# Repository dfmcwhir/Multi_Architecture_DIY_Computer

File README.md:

# Multi_Architecture_DIY_Computer
A DIY computer system that uses a common backplane with swappable 8-bit CPU and add-on cards<BR><br>

Up front, I will state the following:
  1. I started the project for my own learning and enjoyment. There will be documentation shortfalls and hardware and SW bugs that I missed and/or fixed and forgot about. There will also be plenty of poor design choices and probletunities for improvement. 
  2. Most of the electrical designs borrow ideas/circuits from other peoples work and I have modified them to work in my systems. I will try to make sure I document where I got what from.
  3. For the software and firmware, initially I was doing my own development, but I'm not a coder so I progress was really slow/non-existent. More recently, I have started using AI which has led to a lot of progress. Really all the software and firmware in this project is either a slight modifications of other people's code or done by AI.

<br>
<h2> The Concept </h2>
The initial idea as I wrote it in my notes app was:<br>
<quote>
  <b><i></i>Idea for a retro computer "system" that uses various cards in the ISA format with a passive ISA back plane. Ideally the most of the individual ISA cards will be less that 100mmx100mm for cheaper PCB prices which limits them to 8-bit isa cards.

Ideally cpu and interface cards should be inter changeable, so that interface cards can be used with multiple different types of CPU boards. That may require jumpers/switches to change logic level of some control signals and/or to set address decoding.

Possible CPU cards:
  - 6502 - Based on Ben Eater's design
  - 8085 - Similar to the MiniMax 8085?
  - 8088 - IBM XT compatible-ish
  - 6809 - based on Grant Searle's design 
  - Z80 - TRS-80 compatible?
  - ESP32 - For giggles - Would need some sort of multiplexing/latching to generate the data, address, and control busses from the GPIO pins
  - ATMEGA328? - For giggles - Would need some sort of multiplexing/latching to generate the data, address, and control busses from the GPIO pins 

Possible interface cards:
  - Retro video card - MC6847 based. Similar to Kiran Tomlinson's blog post
  - Atmel based keyboard/display/serial - Based on Grant Searle's design
  - Memory expansion
  - Storage controller - ideally the overall system would be compatible with the PicoMem I/O card but a dedicated storage controller maybe required/desired.
</b></i>
</quote>
<br>
So far I have done the 6502 and 8085 CPU cards with the Z80 on the way. The plans for the add-cards changed over time, I didn't do all the ones listed (yet), but I have a number of others. Most of them have ISA_6502 in the name, because that is the CPU I started with, but should at least theoretically be compatible with other CPU cards if they are designed to interface with the bus as I have defined it and with the correct software.

<h2> The "ISA" Bus </h2>
<p>To make it very clear, I am using the physical ISA bus for interfacing but in no way indicating that it meets any ISA specification or standards. Putting a normal ISA card into the system will almost definitely not work and may damage everything. </p>
<p>With that out of the way, when I started designing the system, I tried to match the functions of the signals of my card to the signals functions/names of the standard ISA bus. The idea being, that it would make it easier to insure CPU card compatibility with the add-on cards that way. The matching to the standard ISA pin functions has drifted over time.</p>

<H2>Current bus description</H2>
<table><thead><tr><th>Pin</th><th>Name</th><th>Dir</th><th>Description</th></tr></thead><tbody>
<tr><td>A1</td><td>/I/O CH CK</td><td>IN</td><td>/IOen. Active low; indicates an I/O operation</td></tr>
<tr><td>A2</td><td>D7</td><td>IN/OUT</td><td>Data bit 7</td></tr>
<tr><td>A3</td><td>D6</td><td>IN/OUT</td><td>Data bit 6</td></tr>
<tr><td>A4</td><td>D5</td><td>IN/OUT</td><td>Data bit 5</td></tr>
<tr><td>A5</td><td>D4</td><td>IN/OUT</td><td>Data bit 4</td></tr>
<tr><td>A6</td><td>D3</td><td>IN/OUT</td><td>Data bit 3</td></tr>
<tr><td>A7</td><td>D2</td><td>IN/OUT</td><td>Data bit 2</td></tr>
<tr><td>A8</td><td>D1</td><td>IN/OUT</td><td>Data bit 1</td></tr>
<tr><td>A9</td><td>D0</td><td>IN/OUT&gt;</td><td>Data bit 0</td></tr>
<tr><td>A10</td><td>I/O CH RDY</td><td>IN</td><td>IOrdy or /WAIT, pulled low to lengthen memory cycles or pause the CPU (depending on the CPU card)*</td></tr>
<tr><td>A11</td><td>AEN</td><td>OUT</td><td>Address enable; Not currently used</td></tr>
<tr><td>A12</td><td>A19</td><td>OUT</td><td>Address bit 19 or BA19; Used for memory bank selection</td></tr>
<tr><td>A13</td><td>A18</td><td>OUT</td><td>Address bit 18 or BA18; Used for memory bank selection</td></tr>
<tr><td>A14</td><td>A17</td><td>OUT</td><td>Address bit 17 or BA17; Used for memory bank selection</td></tr>
<tr><td>A15</td><td>A16</td><td>OUT</td><td>Address bit 16 or BA19; Used for memory bank selection</td></tr>
<tr><td>A16</td><td>A15</td><td>OUT</td><td>Address bit 15</td></tr>
<tr><td>A17</td><td>A14</td><td>OUT</td><td>Address bit 14</td></tr>
<tr><td>A18</td><td>A13</td><td>OUT</td><td>Address bit 13</td></tr>
<tr><td>A19</td><td>A12</td><td>OUT</td><td>Address bit 12</td></tr>
<tr><td>A20</td><td>A11</td><td>OUT</td><td>Address bit 11</td></tr>
<tr><td>A21</td><td>A10</td><td>OUT</td><td>Address bit 10</td></tr>
<tr><td>A22</td><td>A9</td><td>OUT</td><td>Address bit 9</td></tr>
<tr><td>A23</td><td>A8</td><td>OUT</td><td>Address bit 8</td></tr>
<tr><td>A24</td><td>A7</td><td>OUT</td><td>Address bit 7</td></tr>
<tr><td>A25</td><td>A6</td><td>OUT</td><td>Address bit 6</td></tr>
<tr><td>A26</td><td>A5</td><td>OUT</td><td>Address bit 5</td></tr>
<tr><td>A27</td><td>A4</td><td>OUT</td><td>Address bit 4</td></tr>
<tr><td>A28</td><td>A3</td><td>OUT</td><td>Address bit 3</td></tr>
<tr><td>A29</td><td>A2</td><td>OUT</td><td>Address bit 2</td></tr>
<tr><td>A30</td><td>A1</td><td>OUT</td><td>Address bit 1</td></tr>
<tr><td>A31</td><td>A0</td><td>OUT</td><td>Address bit 0</td></tr>
<tr><td>B1</td><td><abbr title="Ground">GND</abbr></td><td>Ground</td><td></td>
</tr><tr><td>B2</td><td>RESET</td><td>OUT</td><td>Active low to reset or initialize system logic</td></tr>
<tr><td>B3</td><td>+5V</td><td>+5 <abbr title="Volts Direct Current">VDC</abbr></td><td></td></tr>
<tr><td>B4</td><td>IRQ2</td><td>IN</td><td>Interrupt Request 2; I/O card </td></tr>
<tr><td>B5</td><td>-5VDC</td><td>-5 VDC</td><td>Not Currently used</td></tr>
<tr><td>B6</td><td>DRQ2</td><td>IN</td><td>/DMA; Not used/tested by any add-on cards yet, but should put CPU in state for DMA operations*</td></tr>
<tr><td>B7</td><td>-12VDC</td><td>-12 VDC</td><td>Not Currently used</td></tr>
<tr><td>B8</td><td>/NOWS</td><td>IN</td><td>/STRETCH (CLK stretch); When Low should slow down the clock*</td></tr>
<tr><td>B9</td><td>+12VDC</td><td>+12 VDC</td><td>Not Currently used</td></tr>
<tr><td>B10</td><td>GND</td><td>Ground</td><td></td></tr>
<tr><td>B11</td><td>/SMEMW</td><td>OUT</td><td>Originally intended as /MEMw, but may now be a general Write*</td></tr>
<tr><td>B12</td><td>/SMEMR</td><td>OUT</td><td>Originally intended as /MEMr, but may now be a general Read*</td></tr>
<tr><td>B13</td><td>/IOW</td><td>OUT</td><td>/IOw (/IOen + /Write)*</td></tr>
<tr><td>B14</td><td>/IOR</td><td>OUT</td><td>/IOr (/IOen + /Read + Clk)*</td></tr>
<tr><td>B15</td><td>/DACK3</td><td>OUT</td><td>Not currently used</td></tr>
<tr><td>B16</td><td>DRQ3</td><td>IN</td><td>Not currently used</td></tr>
<tr><td>B17</td><td>/DACK1</td><td>OUT</td><td>Not currently used</td></tr>
<tr><td>B18</td><td>DRQ1</td><td>IN</td><td>Not currently used</td></tr>
<tr><td>B19</td><td>/REFRESH</td><td>IN/OUT</td><td>Not currently used</td></tr>
<tr><td>B20</td><td>CLOCK</td><td>OUT</td><td>/CLK (inverted clock)</td></tr>
<tr><td>B21</td><td>IRQ7</td><td>IN</td><td>Interrupt Request 7, Possibly sound card or SPI interface</td></tr>
<tr><td>B22</td><td>IRQ6</td><td>IN</td><td>Interrupt Request 6; Possibly display/kb</td></tr>
<tr><td>B23</td><td>IRQ5</td><td>IN</td><td>Interrupt Request 5; Usually KB/Display</td></tr>
<tr><td>B24</td><td>IRQ4</td><td>IN</td><td>Interrupt Request 4; I/O card I2C interface</td></tr>
<tr><td>B25</td><td>IRQ3</td><td>IN</td><td>Interrupt Request 3; Serial Card</td></tr>
<tr><td>B26</td><td>/DACK2</td><td>OUT</td><td>Not currently used</td></tr>
<tr><td>B27</td><td>T/C</td><td>OUT</td><td>Raw oscilator clock (2 x CLK) on some CPU cards(</td></tr>
<tr><td>B28</td><td>ALE</td><td>OUT</td><td>Not currently used</td></tr>
<tr><td>B29</td><td>+5V</td><td>+5 VDC</td><td></td></tr>
<tr><td>B30</td><td>OSC</td><td>OUT</td><td>CLK used by CPU and most circuits. In some CPU cards it is 1/2 of the osc frequency</td></tr>
<tr><td>B31</td><td>GND</td><td>Ground</td><td></td></tr>
<tr><td></td><td></td><td></td><td></td></tr>
</tbody></table>
<h3>Notes about some signals:</h3>
<p> /MEMw and /MEMr were initially derived from the R/nW signal on the 6502 card and either /ROMen or /RAMen. As things got more complex, it became necessary to have read and write signals that were available during I/O operations (/IOen) but were not connected to the clock. So now /MEMw and /MEMr on the bus could (depending on the CPU card) be active anytime either an I/O or Memory operation is happening. This means that add-on cards, if a memory read or write is needed, the /MEMw and MEMr signals should be qualified as being in memory by the address or at least by /IOen not being active.</p>
<p>The way /IOr is used on some add-on cards requires it to be active only when the CLK is high, so that is the way it is decoded on the bus. If a read from I/O that isn't dependent on the CLK being high is required (also required on some cards) then a local /read should be decoded from the /IOen and MEMr or /IOen and /IOw not active. /IOw is independent from the clk</p>
<p>Initially the /DMA (/DRQ2) signal was provided for simple DMA operations that Ben Eater describes for his VGA card implementaion. I have never used it and it maybe incompatible with some CPU cards.</p>
<p>IOrdy (or /WAIT) and /STRETCH were implemented on the 6502 CPU Rev2 card and haven't been tested yet. The difference is that /WAIT stops the CPU but CLK and /CLK continue to run. /Stretch stops CLK and /CLK. An Add-card would assert /Stretch then use the TC (2XOSC) raw oscillator signal to count some number of cycles before de-asserting it. On some CPU cards neither signal is implemented at all (like the 8085 CPU Rev1) and on others (like the Z80 CPU rev1) /STRETCH and /WAIT are the same (both are /STRETCH). I don't think any cards require these signals/features if operated at <4MHz. </p>

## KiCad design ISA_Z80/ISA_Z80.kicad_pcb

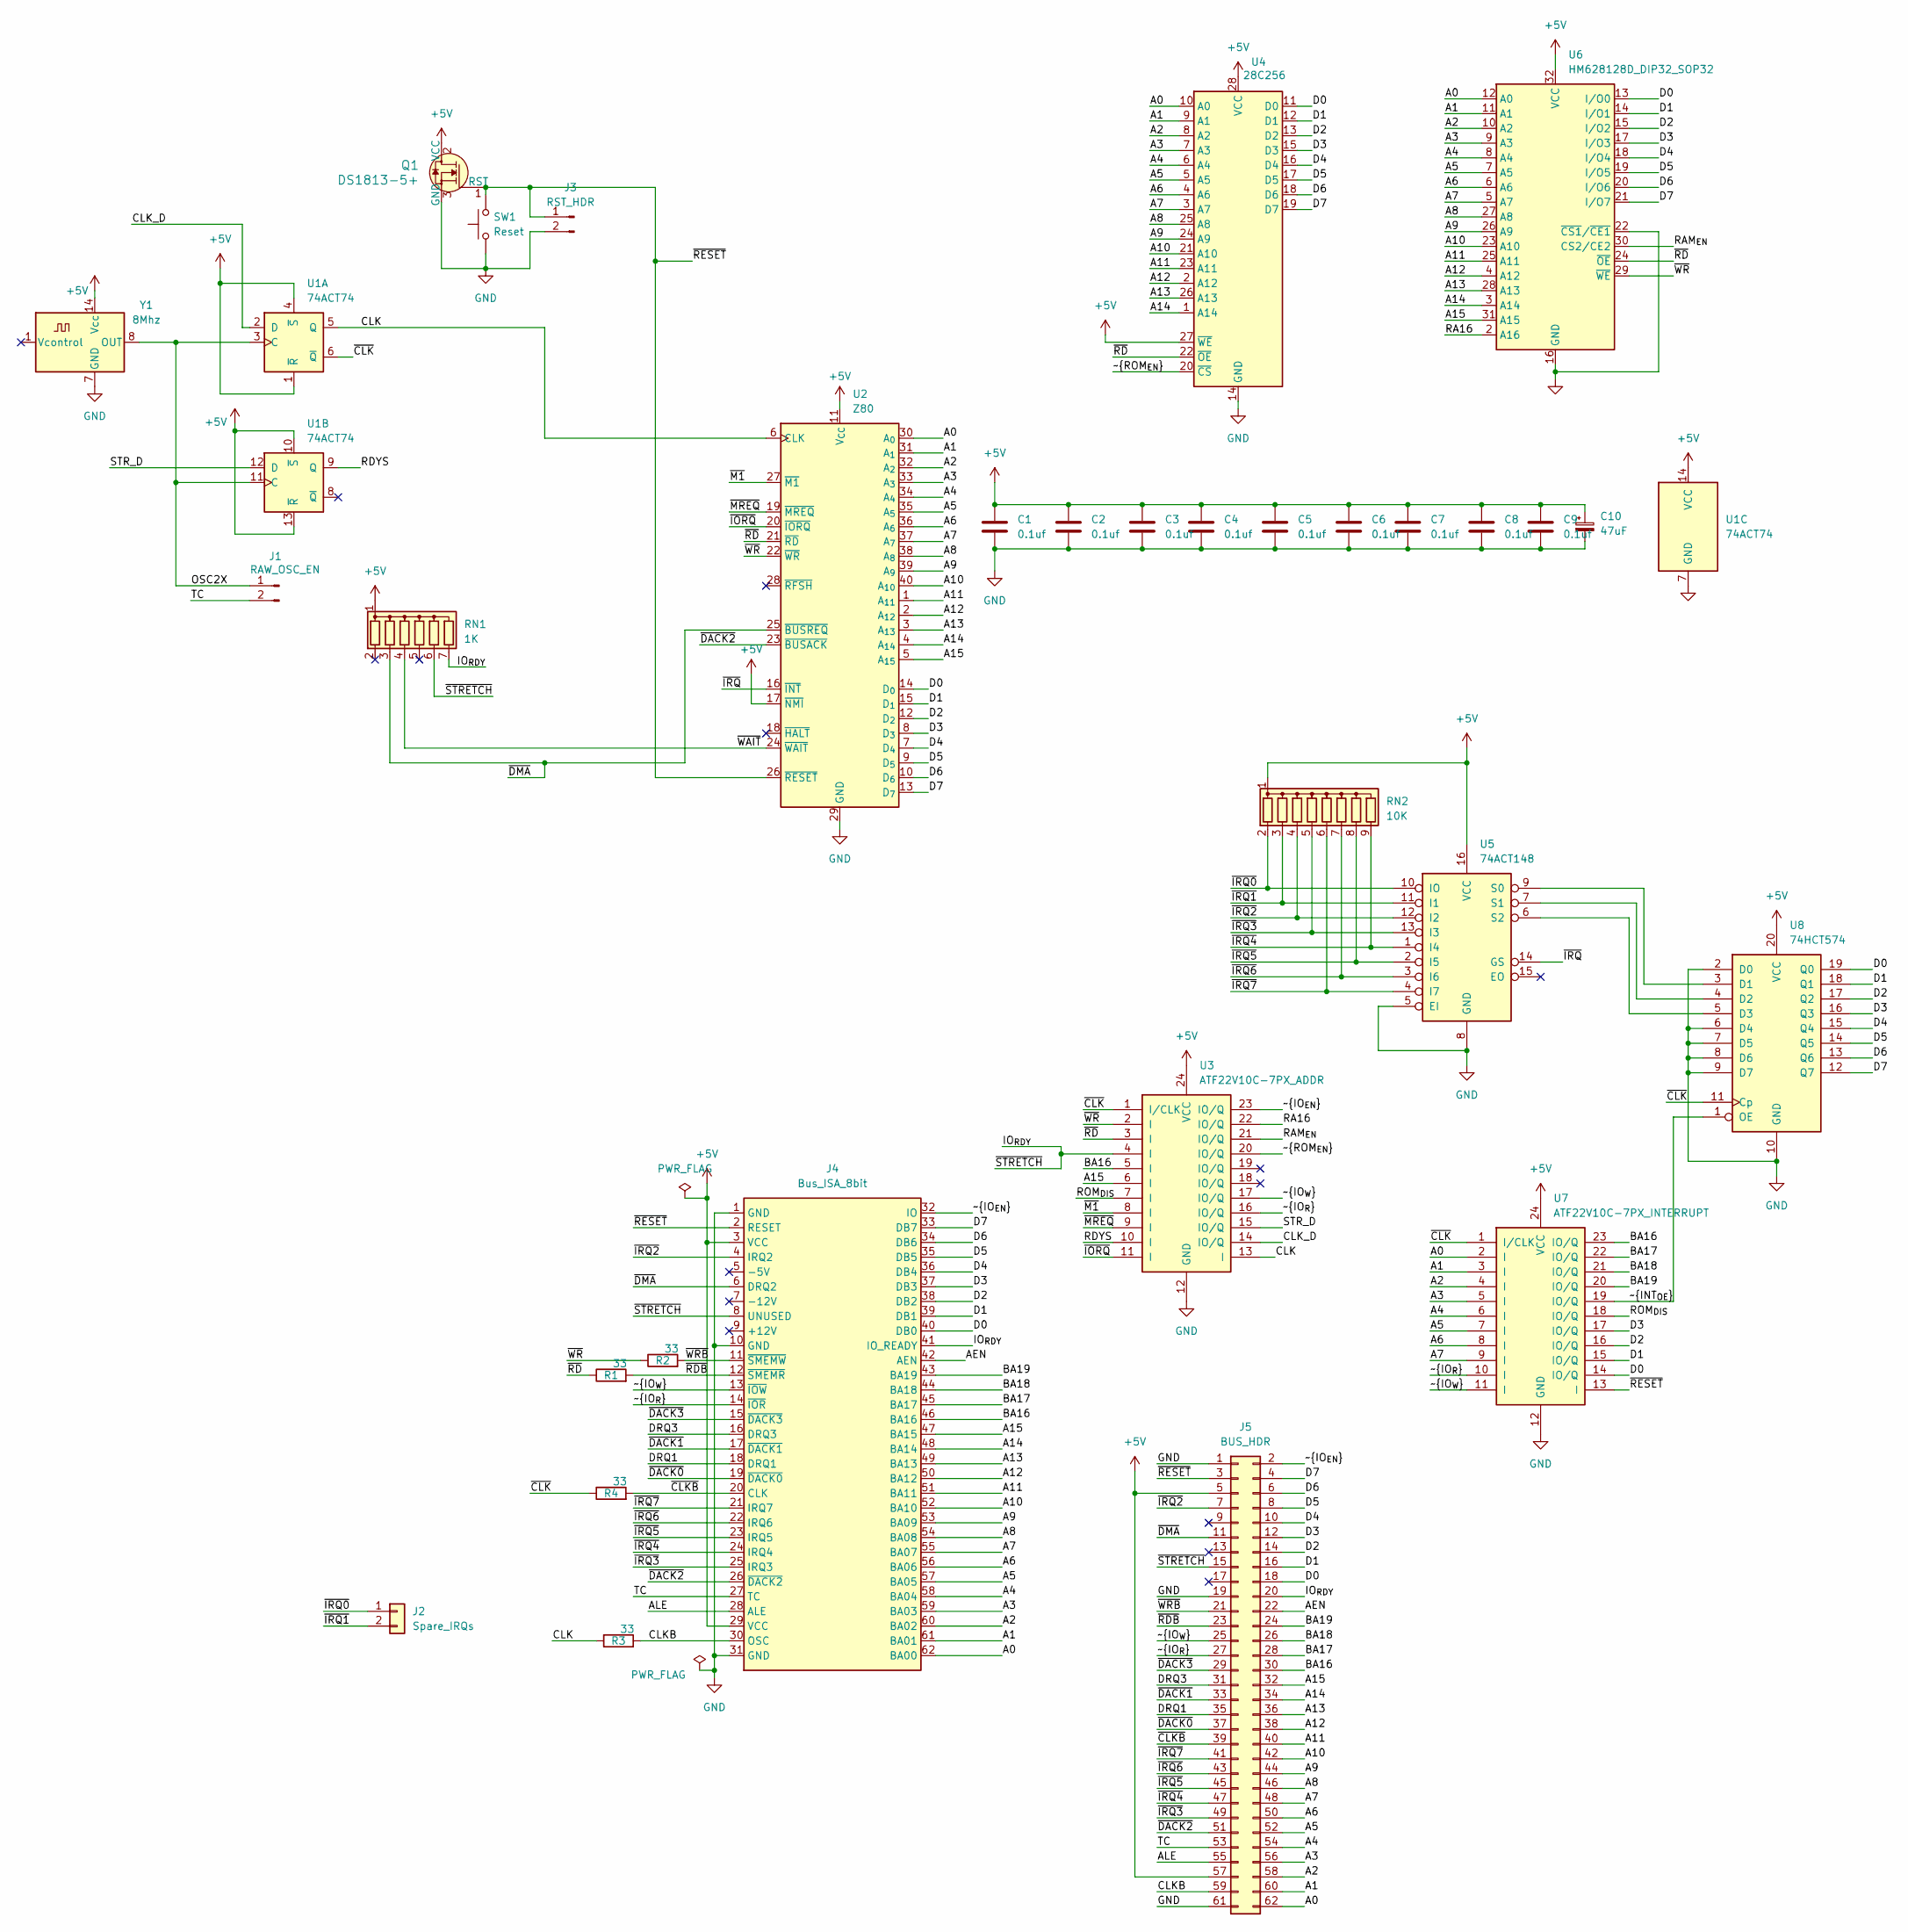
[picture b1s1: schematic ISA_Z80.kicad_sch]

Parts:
C1, C2, C3, C4, C5, C6, C7, C8, C9: 0.1uf; C_Disc_D4.7mm_W2.5mm_P5.00mm
C10: 47uF; CP_Radial_D5.0mm_P2.00mm
J1: RAW_OSC_EN; PinHeader_1x02_P2.54mm_Vertical
J2: Spare_IRQs; PinHeader_1x02_P2.54mm_Vertical
J3: RST_HDR; PinHeader_1x02_P2.54mm_Vertical
J4: Bus_ISA_8bit; BUS_8-bit_ISA
J5: BUS_HDR; PinHeader_2x31_P2.54mm_Vertical
Q1: DS1813-5+; TO-92L_Wide; MPN DS1813-5+-ND; Digi-Key_PN DS1813-5+-ND
R1, R2, R3, R4: 33; R_Axial_DIN0207_L6.3mm_D2.5mm_P10.16mm_Horizontal
RN1: 1K; R_Array_SIP7
RN2: 10K; R_Array_SIP9
SW1: Reset; SW_PUSH_6mm
U1: 74ACT74; DIP-14_W7.62mm
U2: Z80; DIP-40_W15.24mm
U3: ATF22V10C-7PX_ADDR; DIP-24_W7.62mm
U4: 28C256; DIP-28_W15.24mm
U5: 74ACT148; DIP-16_W7.62mm
U6: HM628128D_DIP32_SOP32; DIP-32_W15.24mm
U7: ATF22V10C-7PX_INTERRUPT; DIP-24_W7.62mm
U8: 74HCT574; DIP-20_W7.62mm
Y1: 8Mhz; Oscillator_DIP-14

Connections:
+5V: C1.1, C2.1, C3.1, C4.1, C5.1, C6.1, C7.1, C8.1, C9.1, C10.1, J4.3 (VCC), J4.29 (VCC), J5.5, J5.57, Q1.2 (VCC), RN1.1 (common), RN2.1 (common), U1.1 (~R), U1.4 (~S), U1.10 (~S), U1.13 (~R), U1.14 (VCC), U2.11 (V_{CC}), U2.17 (~NMI), U3.24 (VCC), U4.27 (~WE), U4.28 (VCC), U5.16 (VCC), U6.32 (VCC), U7.24 (VCC), U8.20 (VCC), Y1.14 (Vcc)
/A0: J4.62 (BA00), J5.62, U2.30 (A_{0}), U4.10 (A0), U6.12 (A0), U7.2 (I)
/A1: J4.61 (BA01), J5.60, U2.31 (A_{1}), U4.9 (A1), U6.11 (A1), U7.3 (I)
/A2: J4.60 (BA02), J5.58, U2.32 (A_{2}), U4.8 (A2), U6.10 (A2), U7.4 (I)
/A3: J4.59 (BA03), J5.56, U2.33 (A_{3}), U4.7 (A3), U6.9 (A3), U7.5 (I)
/A4: J4.58 (BA04), J5.54, U2.34 (A_{4}), U4.6 (A4), U6.8 (A4), U7.6 (I)
/A5: J4.57 (BA05), J5.52, U2.35 (A_{5}), U4.5 (A5), U6.7 (A5), U7.7 (I)
/A6: J4.56 (BA06), J5.50, U2.36 (A_{6}), U4.4 (A6), U6.6 (A6), U7.8 (I)
/A7: J4.55 (BA07), J5.48, U2.37 (A_{7}), U4.3 (A7), U6.5 (A7), U7.9 (I)
/A8: J4.54 (BA08), J5.46, U2.38 (A_{8}), U4.25 (A8), U6.27 (A8)
/A9: J4.53 (BA09), J5.44, U2.39 (A_{9}), U4.24 (A9), U6.26 (A9)
/A10: J4.52 (BA10), J5.42, U2.40 (A_{10}), U4.21 (A10), U6.23 (A10)
/A11: J4.51 (BA11), J5.40, U2.1 (A_{11}), U4.23 (A11), U6.25 (A11)
/A12: J4.50 (BA12), J5.38, U2.2 (A_{12}), U4.2 (A12), U6.4 (A12)
/A13: J4.49 (BA13), J5.36, U2.3 (A_{13}), U4.26 (A13), U6.28 (A13)
/A14: J4.48 (BA14), J5.34, U2.4 (A_{14}), U4.1 (A14), U6.3 (A14)
/A15: J4.47 (BA15), J5.32, U2.5 (A_{15}), U3.6 (I), U6.31 (A15)
/AEN: J4.42 (AEN), J5.22
/ALE: J4.28 (ALE), J5.55
/BA16: J4.46 (BA16), J5.30, U3.5 (I), U7.23 (IO/Q)
/BA17: J4.45 (BA17), J5.28, U7.22 (IO/Q)
/BA18: J4.44 (BA18), J5.26, U7.21 (IO/Q)
/BA19: J4.43 (BA19), J5.24, U7.20 (IO/Q)
/CLK: R3.1, U1.5 (Q), U2.6 (CLK), U3.13 (I)
/CLKB: J4.30 (OSC), J5.59, R3.2
/CLK_D: U1.2 (D), U3.14 (IO/Q)
/D0: J4.40 (DB0), J5.18, U2.14 (D_{0}), U4.11 (D0), U6.13 (I/O0), U7.14 (IO/Q), U8.19 (Q0)
/D1: J4.39 (DB1), J5.16, U2.15 (D_{1}), U4.12 (D1), U6.14 (I/O1), U7.15 (IO/Q), U8.18 (Q1)
/D2: J4.38 (DB2), J5.14, U2.12 (D_{2}), U4.13 (D2), U6.15 (I/O2), U7.16 (IO/Q), U8.17 (Q2)
/D3: J4.37 (DB3), J5.12, U2.8 (D_{3}), U4.15 (D3), U6.17 (I/O3), U7.17 (IO/Q), U8.16 (Q3)
/D4: J4.36 (DB4), J5.10, U2.7 (D_{4}), U4.16 (D4), U6.18 (I/O4), U8.15 (Q4)
/D5: J4.35 (DB5), J5.8, U2.9 (D_{5}), U4.17 (D5), U6.19 (I/O5), U8.14 (Q5)
/D6: J4.34 (DB6), J5.6, U2.10 (D_{6}), U4.18 (D6), U6.20 (I/O6), U8.13 (Q6)
/D7: J4.33 (DB7), J5.4, U2.13 (D_{7}), U4.19 (D7), U6.21 (I/O7), U8.12 (Q7)
/DRQ1: J4.18 (DRQ1), J5.35
/DRQ3: J4.16 (DRQ3), J5.31
/IO_{RDY}: J4.8 (UNUSED), J4.41 (IO_READY), J5.15, J5.20, RN1.6 (R5), RN1.7 (R6), U3.4 (I)
/OSC2X: J1.1, U1.3 (C), U1.11 (C), Y1.8 (OUT)
/RA16: U3.22 (IO/Q), U6.2 (A16)
/RAM_{EN}: U3.21 (IO/Q), U6.30 (CS2/CE2)
/RDYS: U1.9 (Q), U3.10 (I)
/ROM_{DIS}: U3.7 (I), U7.18 (IO/Q)
/STR_D: U1.12 (D), U3.15 (IO/Q)
/TC: J1.2, J4.27 (TC), J5.53
/~CLKB: J4.20 (CLK), J5.39, R4.2
/~CLK: R4.1, U1.6 (~Q), U3.1 (I/CLK), U7.1 (I/CLK), U8.11 (Cp)
/~DACK0: J4.19 (~DACK0), J5.37
/~DACK1: J4.17 (~DACK1), J5.33
/~DACK2: J4.26 (~DACK2), J5.51, U2.23 (~BUSACK)
/~DACK3: J4.15 (~DACK3), J5.29
/~DMA: J4.6 (DRQ2), J5.11, RN1.3 (R2), U2.25 (~BUSREQ)
/~INT_{OE}: U7.19 (IO/Q), U8.1 (OE)
/~IORQ: U2.20 (~IORQ), U3.11 (I)
/~IO_{EN}: J4.32 (IO), J5.2, U3.23 (IO/Q)
/~IO_{R}: J4.14 (~IOR), J5.27, U3.16 (IO/Q), U7.10 (I)
/~IO_{W}: J4.13 (~IOW), J5.25, U3.17 (IO/Q), U7.11 (I)
/~IRQ0: J2.1, RN2.2 (R1), U5.10 (IO)
/~IRQ1: J2.2, RN2.3 (R2), U5.11 (I1)
/~IRQ2: J4.4 (IRQ2), J5.7, RN2.4 (R3), U5.12 (I2)
/~IRQ3: J4.25 (IRQ3), J5.49, RN2.5 (R4), U5.13 (I3)
/~IRQ4: J4.24 (IRQ4), J5.47, RN2.9 (R8), U5.1 (I4)
/~IRQ5: J4.23 (IRQ5), J5.45, RN2.8 (R7), U5.2 (I5)
/~IRQ6: J4.22 (IRQ6), J5.43, RN2.7 (R6), U5.3 (I6)
/~IRQ7: J4.21 (IRQ7), J5.41, RN2.6 (R5), U5.4 (I7)
/~IRQ: U2.16 (~INT), U5.14 (GS)
/~M1: U2.27 (~M1), U3.8 (I)
/~MREQ: U2.19 (~MREQ), U3.9 (I)
/~RDB: J4.12 (~SMEMR), J5.23, R1.2
/~RD: R1.1, U2.21 (~RD), U3.3 (I), U4.22 (~OE), U6.24 (~OE)
/~RESET: J3.1, J4.2 (RESET), J5.3, Q1.1 (RST), SW1.2, U2.26 (~RESET), U7.13 (I)
/~ROM_{EN}: U3.20 (IO/Q), U4.20 (~CS)
/~WAIT: RN1.4 (R3), U2.24 (~WAIT)
/~WRB: J4.11 (~SMEMW), J5.21, R2.2
/~WR: R2.1, U2.22 (~WR), U3.2 (I), U6.29 (~WE)
GND: C1.2, C2.2, C3.2, C4.2, C5.2, C6.2, C7.2, C8.2, C9.2, C10.2, J3.2, J4.1 (GND), J4.10 (GND), J4.31 (GND), J5.1, J5.19, J5.61, Q1.3 (GND), SW1.1, U1.7 (GND), U2.29 (GND), U3.12 (GND), U4.14 (GND), U5.5 (EI), U5.8 (GND), U6.16 (GND), U6.22 (~CS1/~CE1), U7.12 (GND), U8.2 (D0), U8.6 (D4), U8.7 (D5), U8.8 (D6), U8.9 (D7), U8.10 (GND), Y1.7 (GND)
unnamed: U5.9 (S0), U8.3 (D1)
unnamed: U5.7 (S1), U8.4 (D2)
unnamed: U5.6 (S2), U8.5 (D3)

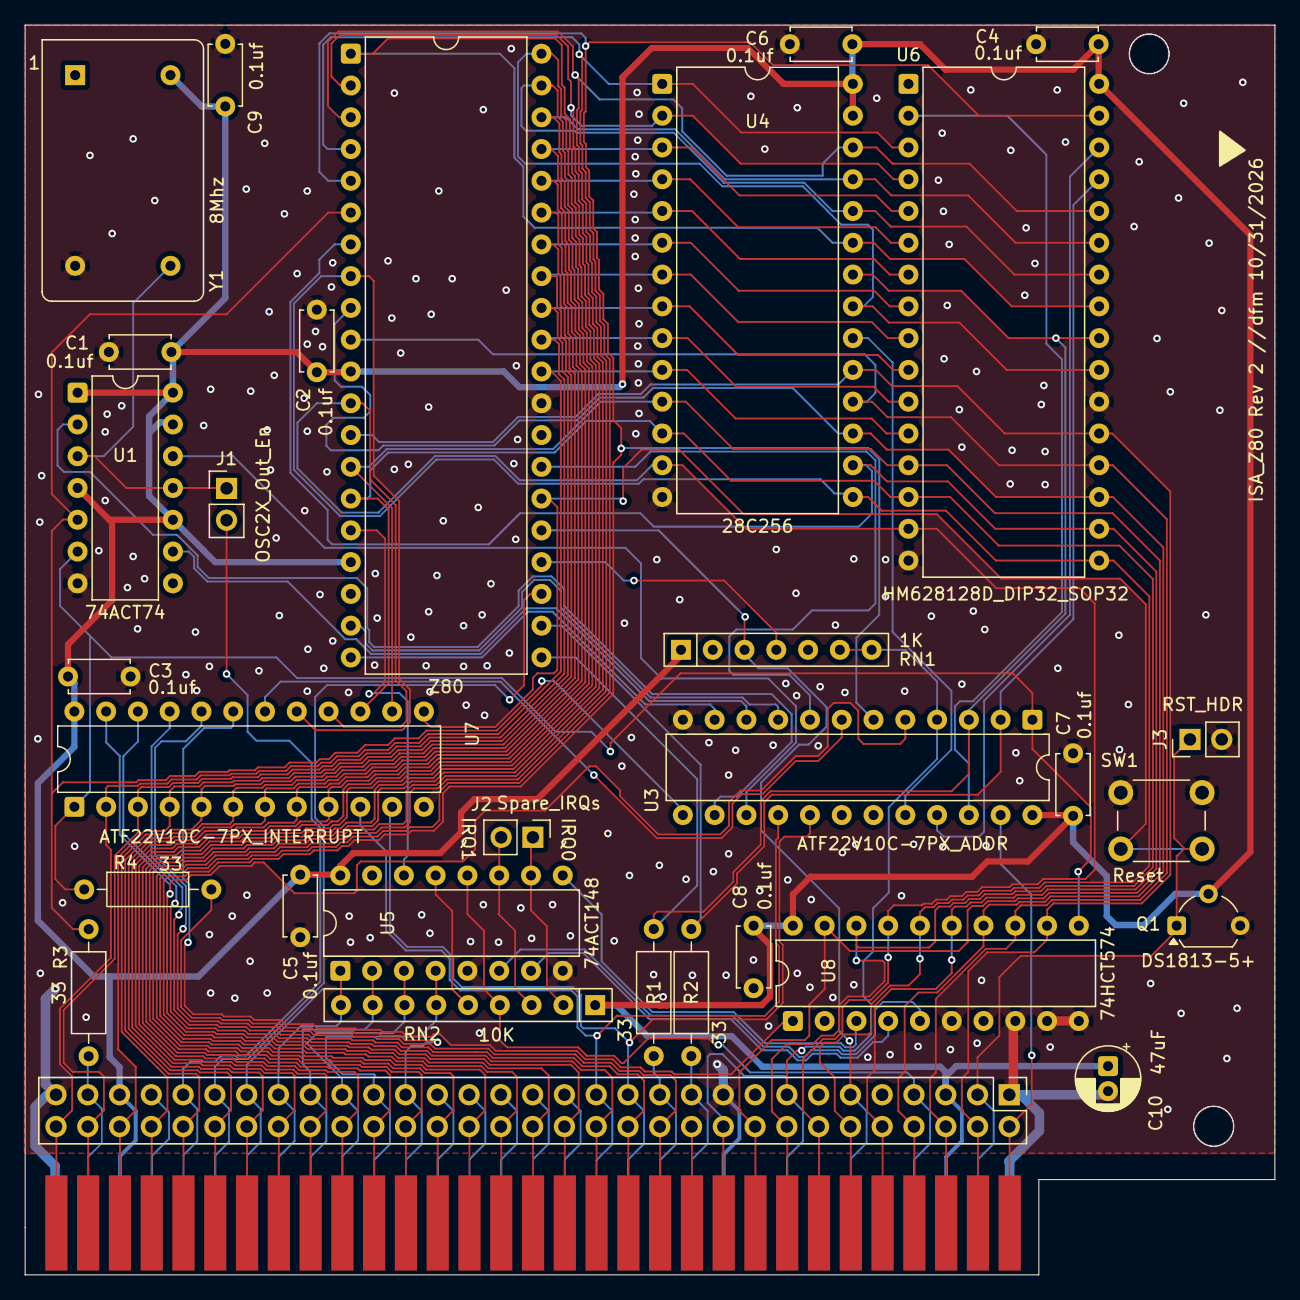
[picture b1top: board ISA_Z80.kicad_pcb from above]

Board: 2 copper layers, 99.9 x 99.9 mm, 32 parts (0 on the bottom side), 78 nets.

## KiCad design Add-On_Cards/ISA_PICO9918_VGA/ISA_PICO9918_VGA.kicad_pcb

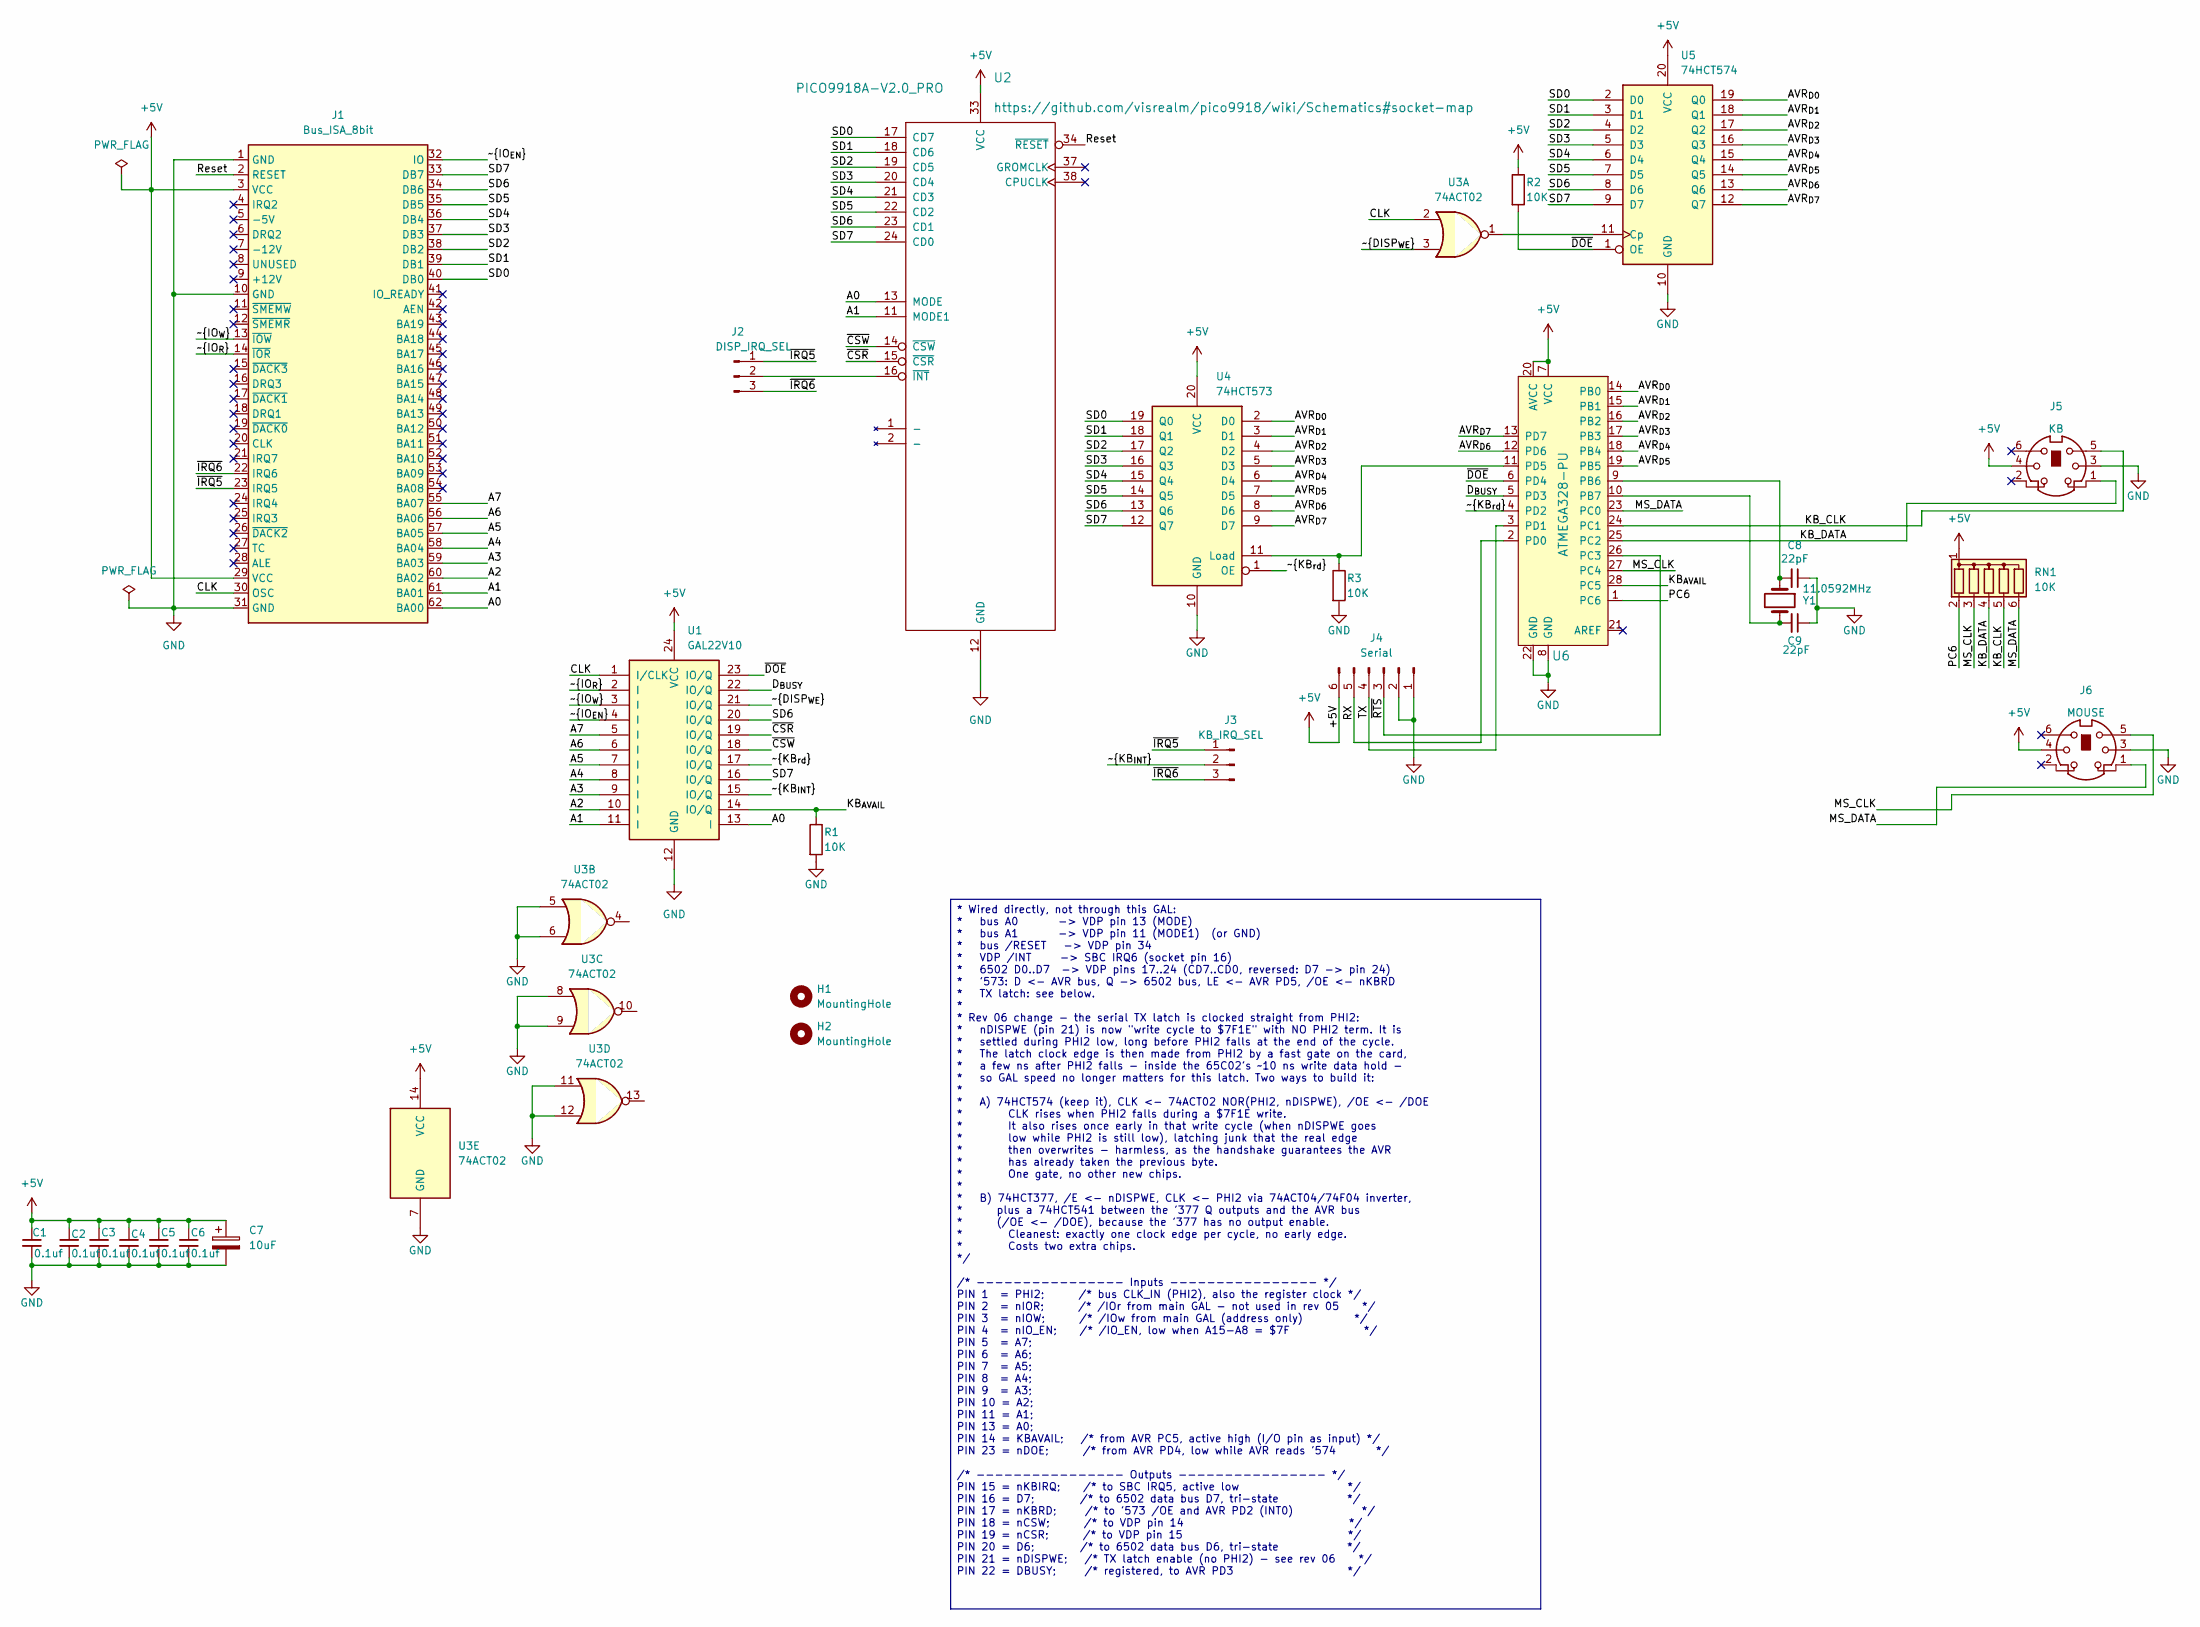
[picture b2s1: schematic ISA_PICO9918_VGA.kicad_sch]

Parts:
C1, C2, C3, C4, C5, C6: 0.1uf; C_Disc_D4.7mm_W2.5mm_P5.00mm; Voltage 50V; Tolerance 5%
C7: 10uF; CP_Radial_D5.0mm_P2.00mm
C8, C9: 22pF; C_Disc_D4.7mm_W2.5mm_P5.00mm; Voltage 50V; Tolerance 5%
H1, H2: MountingHole; MountingHole_3.2mm_M3
J1: Bus_ISA_8bit; BUS_8-bit_ISA_CARD
J2: DISP_IRQ_SEL; PinHeader_1x03_P2.54mm_Vertical
J3: KB_IRQ_SEL; PinHeader_1x03_P2.54mm_Vertical
J4: Serial; PinHeader_1x06_P2.54mm_Vertical
J5: KB; Connector_Mini-DIN_Female_6Pin_2rows
J6: MOUSE; Connector_Mini-DIN_Female_6Pin_2rows
R1, R2, R3: 10K; R_Axial_DIN0207_L6.3mm_D2.5mm_P10.16mm_Horizontal
RN1: 10K; R_Array_SIP6
U1: GAL22V10; DIP-24_W7.62mm
U2: PICO9918A-V2.0_PRO; DIP-40_W15.24mm
U3: 74ACT02; DIP-14_W7.62mm
U4: 74HCT573; DIP-20_W7.62mm
U5: 74HCT574; DIP-20_W7.62mm
U6: ATMEGA328-PU; DIP-28_W7.62mm_Socket; MPN ATMEGA328-PU; Digi-Key_PN ATMEGA328-PU-ND
Y1: 11.0592MHz; Crystal_HC18-U_Vertical

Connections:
+5V: C1.1, C2.1, C3.1, C4.1, C5.1, C6.1, C7.1, J1.3 (VCC), J1.29 (VCC), J4.6, J5.4, J6.4, R2.1, RN1.1 (common), U1.24 (VCC), U2.33 (VCC), U3.14 (VCC), U4.20 (VCC), U5.20 (VCC), U6.7 (VCC), U6.20 (AVCC)
/A0: J1.62 (BA00), U1.13 (I), U2.13 (MODE)
/A1: J1.61 (BA01), U1.11 (I), U2.11 (MODE1)
/A2: J1.60 (BA02), U1.10 (I)
/A3: J1.59 (BA03), U1.9 (I)
/A4: J1.58 (BA04), U1.8 (I)
/A5: J1.57 (BA05), U1.7 (I)
/A6: J1.56 (BA06), U1.6 (I)
/A7: J1.55 (BA07), U1.5 (I)
/AVR_{D0}: U4.2 (D0), U5.19 (Q0), U6.14 (PB0)
/AVR_{D1}: U4.3 (D1), U5.18 (Q1), U6.15 (PB1)
/AVR_{D2}: U4.4 (D2), U5.17 (Q2), U6.16 (PB2)
/AVR_{D3}: U4.5 (D3), U5.16 (Q3), U6.17 (PB3)
/AVR_{D4}: U4.6 (D4), U5.15 (Q4), U6.18 (PB4)
/AVR_{D5}: U4.7 (D5), U5.14 (Q5), U6.19 (PB5)
/AVR_{D6}: U4.8 (D6), U5.13 (Q6), U6.12 (PD6)
/AVR_{D7}: U4.9 (D7), U5.12 (Q7), U6.13 (PD7)
/CLK: J1.30 (OSC), U1.1 (I/CLK), U3.2
/D_{BUSY}: U1.22 (IO/Q), U6.5 (PD3)
/KB_CLK: J5.5, RN1.5 (R4), U6.24 (PC1)
/KB_DATA: J5.1, RN1.4 (R3), U6.25 (PC2)
/KB_{AVAIL}: R1.1, U1.14 (IO/Q), U6.28 (PC5)
/MS_CLK: J6.5, RN1.3 (R2), U6.27 (PC4)
/MS_DATA: J6.1, RN1.6 (R5), U6.23 (PC0)
/PC6: RN1.2 (R1), U6.1 (PC6)
/RX: J4.5, U6.2 (PD0)
/Reset: J1.2 (RESET), U2.34 (~RESET)
/SD0: J1.40 (DB0), U2.17 (CD7), U4.19 (Q0), U5.2 (D0)
/SD1: J1.39 (DB1), U2.18 (CD6), U4.18 (Q1), U5.3 (D1)
/SD2: J1.38 (DB2), U2.19 (CD5), U4.17 (Q2), U5.4 (D2)
/SD3: J1.37 (DB3), U2.20 (CD4), U4.16 (Q3), U5.5 (D3)
/SD4: J1.36 (DB4), U2.21 (CD3), U4.15 (Q4), U5.6 (D4)
/SD5: J1.35 (DB5), U2.22 (CD2), U4.14 (Q5), U5.7 (D5)
/SD6: J1.34 (DB6), U1.20 (IO/Q), U2.23 (CD1), U4.13 (Q6), U5.8 (D6)
/SD7: J1.33 (DB7), U1.16 (IO/Q), U2.24 (CD0), U4.12 (Q7), U5.9 (D7)
/TX: J4.4, U6.3 (PD1)
/~CSR: U1.19 (IO/Q), U2.15 (~CSR)
/~CSW: U1.18 (IO/Q), U2.14 (~CSW)
/~DISP_{WE}: U1.21 (IO/Q), U3.3
/~DOE: R2.2, U1.23 (IO/Q), U5.1 (OE), U6.6 (PD4)
/~IO_{EN}: J1.32 (IO), U1.4 (I)
/~IO_{R}: J1.14 (~IOR), U1.2 (I)
/~IO_{W}: J1.13 (~IOW), U1.3 (I)
/~IRQ5: J1.23 (IRQ5), J2.1, J3.1
/~IRQ6: J1.22 (IRQ6), J2.3, J3.3
/~KB_{INT}: J3.2, U1.15 (IO/Q)
/~KB_{rd}: U1.17 (IO/Q), U4.1 (OE), U6.4 (PD2)
/~RTS: J4.3, U6.26 (PC3)
GND: C1.2, C2.2, C3.2, C4.2, C5.2, C6.2, C7.2, C8.1, C9.1, J1.1 (GND), J1.10 (GND), J1.31 (GND), J4.1, J4.2, J5.3, J6.3, R1.2, R3.2, U1.12 (GND), U2.12 (GND), U3.5, U3.6, U3.7 (GND), U3.8, U3.9, U3.11, U3.12, U4.10 (GND), U5.10 (GND), U6.8 (GND), U6.22 (GND)
unnamed: J2.2, U2.16 (~INT)
unnamed: R3.1, U4.11 (Load), U6.11 (PD5)
unnamed: U3.1, U5.11 (Cp)
unnamed: C8.2, U6.9 (PB6), Y1.1
unnamed: C9.2, U6.10 (PB7), Y1.2

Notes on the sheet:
* Wired directly, not through this GAL: * bus A0 -> VDP pin 13 (MODE) * bus A1 -> VDP pin 11 (MODE1) (or GND) * bus /RESET -> VDP pin 34 * VDP /INT -> SBC IRQ6 (socket pin 16) * 6502 D0..D7 -> VDP pins 17..24 (CD7..CD0, reversed: D7 -> pin 24) * '573: D <- AVR bus, Q -> 6502 bus, LE <- AVR PD5, /OE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

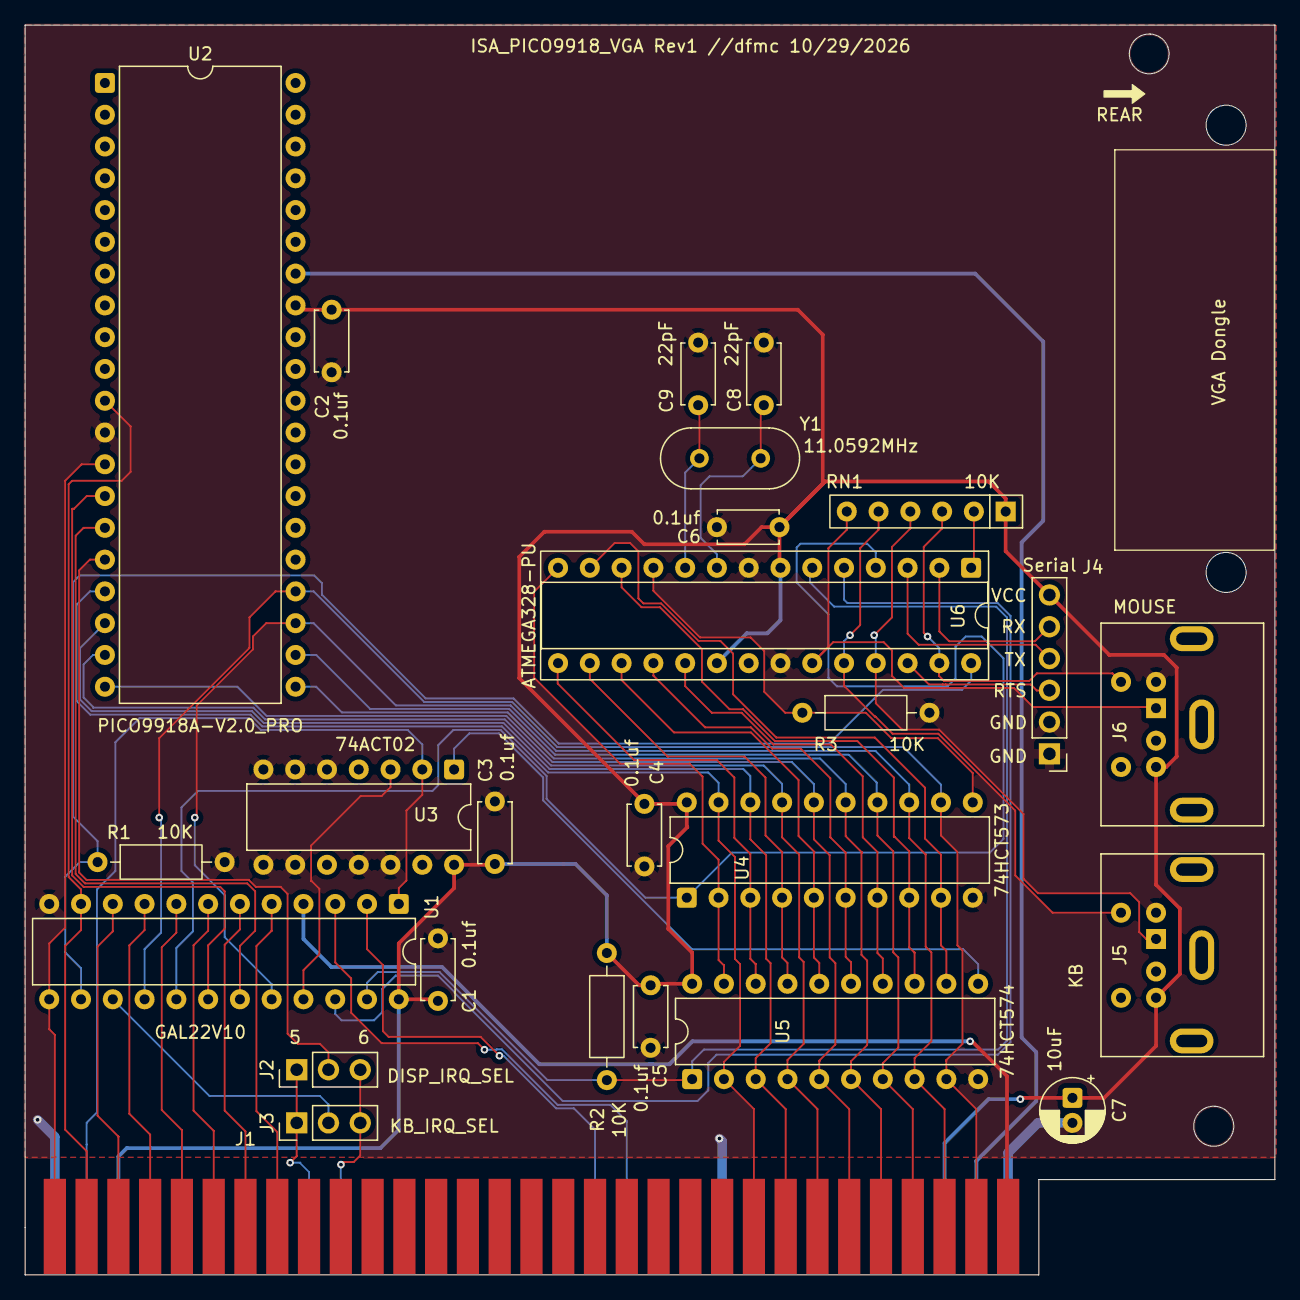
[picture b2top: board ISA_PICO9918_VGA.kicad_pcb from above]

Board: 2 copper layers, 99.9 x 99.9 mm, 28 parts (0 on the bottom side), 54 nets.
